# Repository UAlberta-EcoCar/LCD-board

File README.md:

# LCD-board
LCD board eagle files

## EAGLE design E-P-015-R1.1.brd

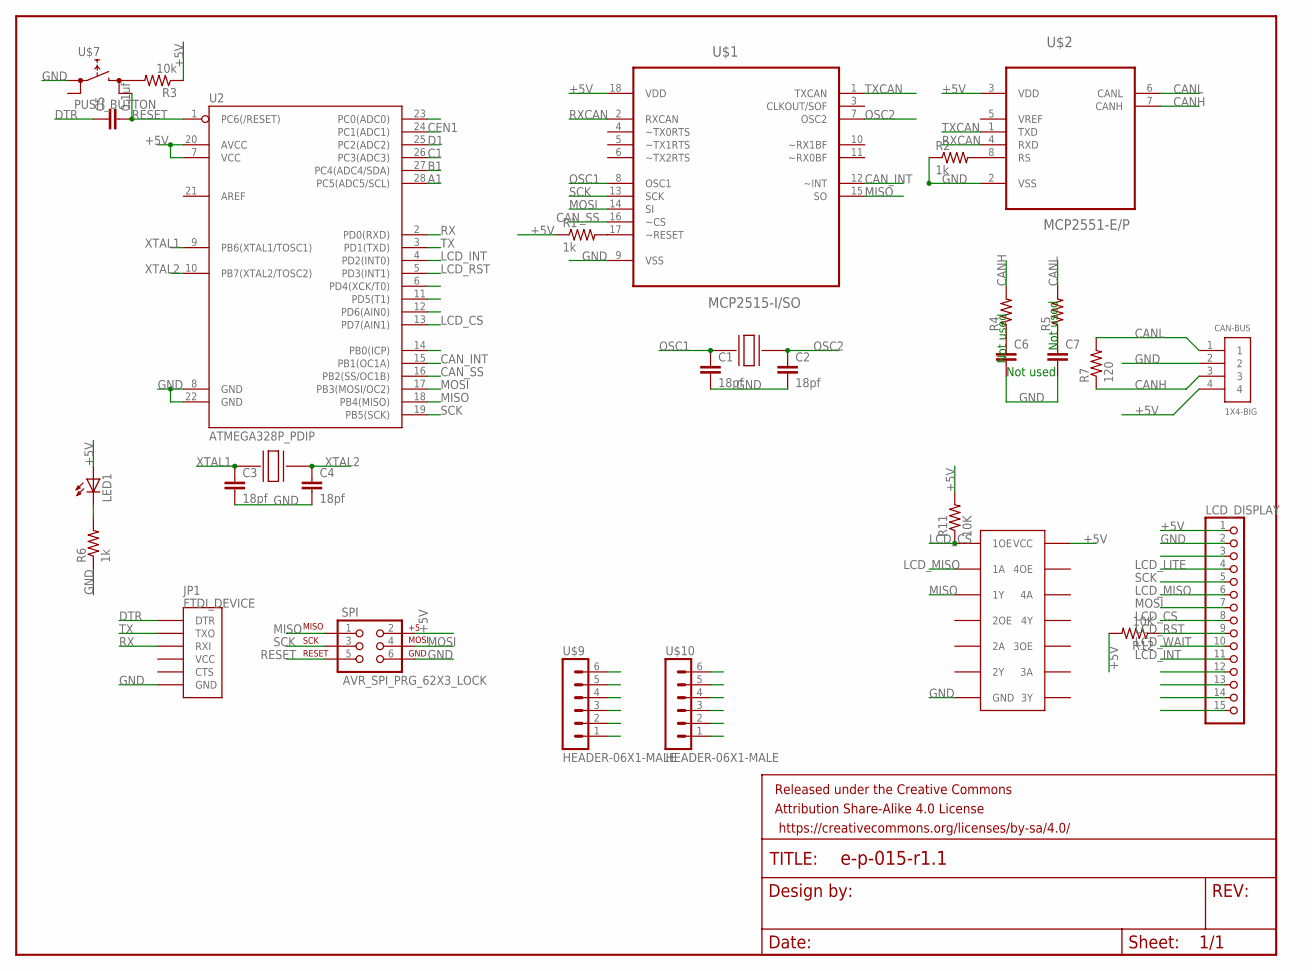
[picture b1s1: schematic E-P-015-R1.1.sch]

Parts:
C1, C2, C3, C4: 18pf; 0805
C5: 0.1uf; 0805
C6, C7: CAP0805; 0805
CAN-BUS: 1X4-BIG; 1X04-BIG
FRAME1: FRAME-LETTERNO_PACKAGE; DUMMY
JP1: FTDI_DEVICE; FTDI_DEVICE_SIDE
LCD_DISPLAY: PINHD-1X15; 1X15
LED1: LEDCHIPLED_1206; CHIPLED_1206
R1, R2, R6: 1k; 0805
R3: 10k; 0805
R4, R5: RESISTOR0805-RES; 0805
R7: 120; M1206
R11, R12: 10K; 0805
SPI: AVR_SPI_PRG_62X3_LOCK; 2X3_LOCK
U2: ATMEGA328P_PDIP; DIL28-3
U$1: MCP2515-I/SO; SOIC127P1034X264-18N
U$2: MCP2551-E/P; DIP254P762X432-8
U$3, U$4: CRYSTAL; 7A_CRYSTAL
U$5: SN74HC125N; 296-1572-5-ND
U$7: PUSH_BUTTON; PUSHBUTTON
U$9, U$10: HEADER-06X1-MALE; 06X1-PTH

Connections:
+5V: CAN-BUS.4, LCD_DISPLAY.1, LED1.A, R1.1, R3.1, R11.2, R12.2, SPI.2, U2.7 (VCC), U2.20 (AVCC), U$1.18 (VDD), U$2.3 (VDD), U$5.P$14 (VCC)
A1: U2.28 (PC5(ADC5/SCL)), U$9.6
A2: U2.23 (PC0(ADC0)), U$10.6
B1: U2.27 (PC4(ADC4/SDA)), U$9.5
B2: U2.6 (PD4(XCK/T0)), U$10.5
C1: U2.26 (PC3(ADC3)), U$9.4
C2: U2.11 (PD5(T1)), U$10.4
CANH: CAN-BUS.3, R4.2, R7.1, U$2.7 (CANH)
CANL: CAN-BUS.1, R5.2, R7.2, U$2.6 (CANL)
CAN_INT: U2.15 (PB1(OC1A)), U$1.12 (~INT)
CAN_SS: U2.16 (PB2(SS/OC1B)), U$1.16 (~CS)
CEN1: U2.24 (PC1(ADC1)), U$9.2
CEN2: U2.14 (PB0(ICP)), U$10.2
D1: U2.25 (PC2(ADC2)), U$9.3
D2: U2.12 (PD6(AIN0)), U$10.3
DTR: C5.1, JP1.P$1 (DTR)
GND: C1.2, C2.2, C3.2, C4.2, C6.2, C7.2, CAN-BUS.2, JP1.P$6 (GND), LCD_DISPLAY.2, R2.1, R6.1, SPI.6, U2.8 (GND), U2.22 (GND), U$1.9 (VSS), U$2.2 (VSS), U$5.P$7 (GND), U$7.L1 (L), U$9.1, U$10.1
LCD_CS: LCD_DISPLAY.8, R11.1, U2.13 (PD7(AIN1)), U$5.P$1 (1OE)
LCD_INT: LCD_DISPLAY.11, U2.4 (PD2(INT0))
LCD_LITE: LCD_DISPLAY.4
LCD_MISO: LCD_DISPLAY.6, U$5.P$2 (1A)
LCD_RST: LCD_DISPLAY.9, R12.1, U2.5 (PD3(INT1))
LCD_WAIT: LCD_DISPLAY.10
MISO: SPI.1, U2.18 (PB4(MISO)), U$1.15 (SO), U$5.P$3 (1Y)
MOSI: LCD_DISPLAY.7, SPI.4, U2.17 (PB3(MOSI/OC2)), U$1.14 (SI)
unnamed: R1.2, U$1.17 (~RESET)
unnamed: R2.2, U$2.8 (RS)
unnamed: C6.1, R4.1
unnamed: R3.2, U$7.R1 (R)
unnamed: C7.1, R5.1
unnamed: LED1.C, R6.2
OSC1: C1.1, U$1.8 (OSC1), U$3.P$2
OSC2: C2.1, U$1.7 (OSC2), U$3.P$1
RESET: C5.2, SPI.5, U2.1 (PC6(/RESET)), U$7.R2 (R)
RX: JP1.P$3 (RXI), U2.2 (PD0(RXD))
RXCAN: U$1.2 (RXCAN), U$2.4 (RXD)
SCK: LCD_DISPLAY.5, SPI.3, U2.19 (PB5(SCK)), U$1.13 (SCK)
TX: JP1.P$2 (TXO), U2.3 (PD1(TXD))
TXCAN: U$1.1 (TXCAN), U$2.1 (TXD)
XTAL1: C3.1, U2.9 (PB6(XTAL1/TOSC1)), U$4.P$2
XTAL2: C4.1, U2.10 (PB7(XTAL2/TOSC2)), U$4.P$1

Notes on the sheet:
Not used

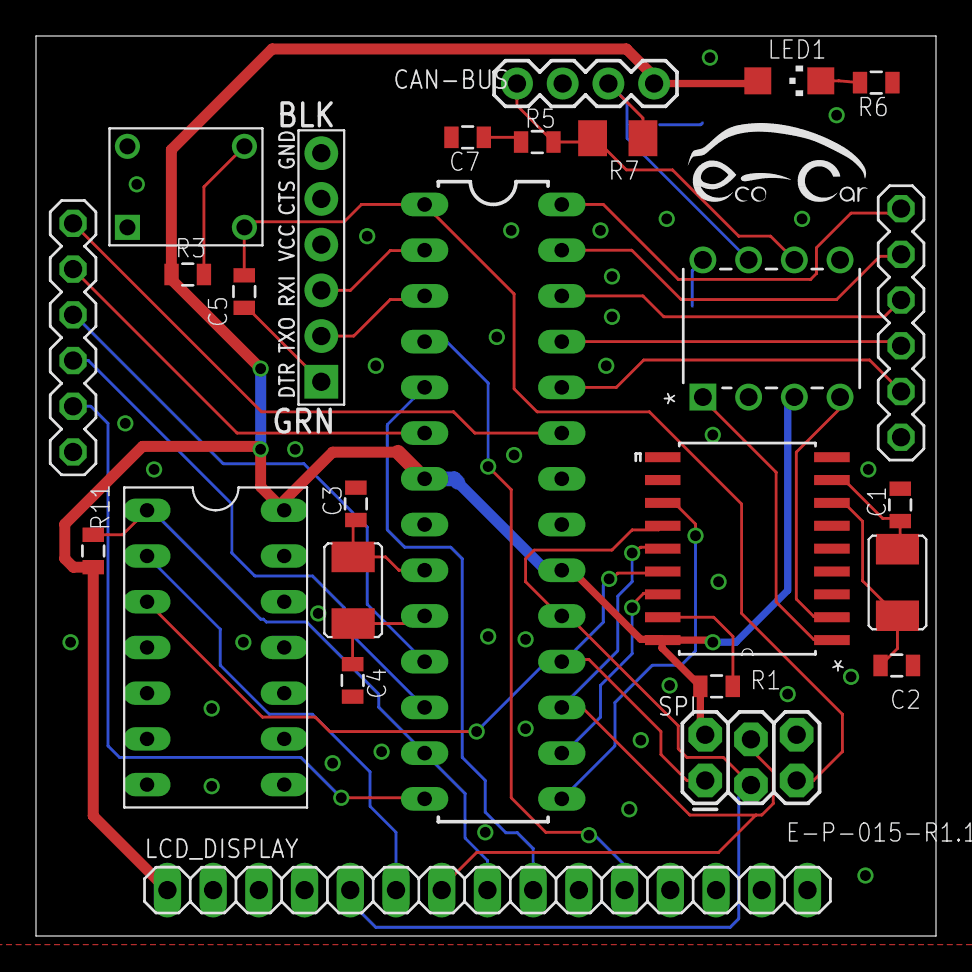
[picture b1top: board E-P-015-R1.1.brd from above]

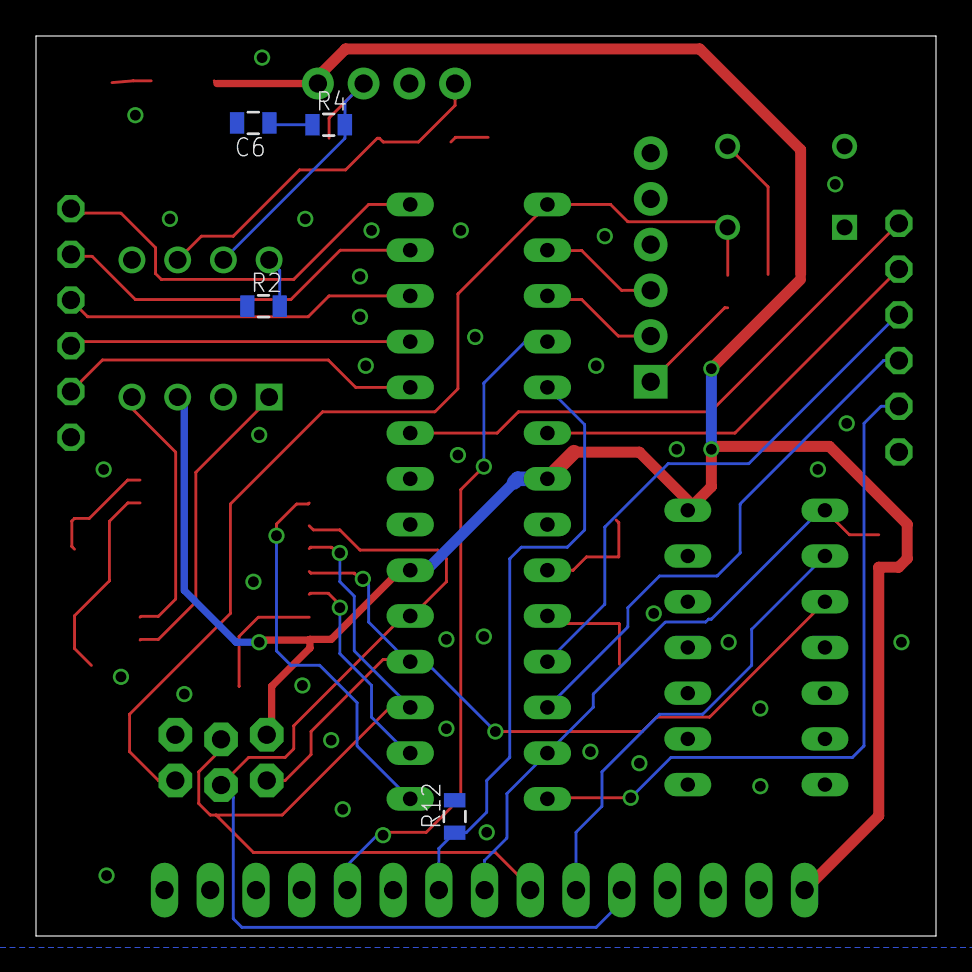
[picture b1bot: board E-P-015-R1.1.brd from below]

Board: 2 copper layers, 50.0 x 50.0 mm, 31 parts (4 on the bottom side), 39 nets.

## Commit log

2016-03-04 Added boards

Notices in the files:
parts and their libraries:
SparkFun-Capacitors: Licensing: Creative Commons ShareAlike 4.0 International - https://creativecommons.org/licenses/by-sa/4.0
SparkFun-Aesthetics: Released under the Creative Commons Attribution Share-Alike 4.0 License
SparkFun-Aesthetics: https://creativecommons.org/licenses/by-sa/4.0
